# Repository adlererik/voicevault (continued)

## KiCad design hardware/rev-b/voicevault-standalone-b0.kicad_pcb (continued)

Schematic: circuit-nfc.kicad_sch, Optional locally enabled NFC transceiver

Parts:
C1001, C1003, C1007, C1009, C1016: 2.2u 10V; C_0603_1608Metric
C1002: 100n 10V; C_0402_1005Metric
C1004, C1006, C1008, C1010, C1013: 10n 10V; C_0402_1005Metric
C1005: 4.7u 10V; C_0603_1608Metric
C1011: 22n 10V; C_0402_1005Metric
C1012: 1u 10V; C_0603_1608Metric
C1014, C1015: 10p C0G; C_0402_1005Metric
R1001: 100k; R_0402_1005Metric
R1002: 47k; R_0402_1005Metric
U7: ST25R3916B-BWLT; ST25R3916B_WLCSP36_REVIEW
U1001: TLV75533PDRVR; TI_DRV0006A_WSON6_2x2_EP1x1p6
X1001: 830108212709 / 27.12MHz CL8pF; Crystal_SMD_2016-4Pin_2.0x1.6mm

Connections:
GND: C1001.2, C1002.2, C1003.2, C1004.2, C1005.2, C1006.2, C1007.2, C1008.2, C1009.2, C1010.2, C1011.2, C1012.2, C1013.2, C1014.2, C1015.2, C1016.2, R1001.2, U7.A3 (GND_A), U7.B3 (GND_A), U7.B4 (GND_A), U7.C1 (VSS), U7.C2 (VSS), U7.C3 (VSS), U7.D2 (I2C_EN), U7.D5 (GND_D), U7.F1 (GND_DR2), U7.F4 (GND_DR1), U1001.3 (GND), U1001.7 (EP_GND), X1001.2 (CASE), X1001.4 (CASE); also elsewhere on the board
NFC_3V3: C1001.1, C1002.1, C1003.1, C1004.1, R1002.2, U7.A6 (VDD_IO), U7.E5 (VDD_TX), U7.E6 (VDD), U1001.1 (OUT); also elsewhere on the board
NFC_AGDC: C1012.1, C1013.1, U7.A2 (AGDC)
NFC_CS_N: R1002.1, U7.A5 (BSS); also elsewhere on the board
NFC_IRQ: U7.A4 (IRQ); also elsewhere on the board
NFC_MISO: U7.B5 (MISO); also elsewhere on the board
NFC_MOSI: U7.D4 (MOSI); also elsewhere on the board
NFC_POWER_EN: R1001.1, U1001.4 (EN); also elsewhere on the board
NFC_RFI1: U7.B1 (RFI1); also elsewhere on the board
NFC_RFI2: U7.B2 (RFI2); also elsewhere on the board
NFC_RFO1: U7.F3 (RFO1); also elsewhere on the board
NFC_RFO2: U7.F2 (RFO2); also elsewhere on the board
NFC_RF_DR: C1005.1, C1006.1, U7.E3 (VDD_DR), U7.F6 (VDD_RF)
NFC_SCK: U7.D3 (SCLK); also elsewhere on the board
NFC_VDD_A: C1009.1, C1010.1, U7.E4 (VDD_A)
NFC_VDD_AM: C1011.1, U7.F5 (VDD_AM)
NFC_VDD_D: C1007.1, C1008.1, U7.C5 (VDD_D)
NFC_XTI: C1014.1, U7.D6 (XTI), X1001.1 (XI)
NFC_XTO: C1015.1, U7.C6 (XTO), X1001.3 (XO)
VSYS: C1016.1, U1001.6 (IN); also elsewhere on the board

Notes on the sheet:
ST25R3916B-BWLT retains Safe7 core part. Supplies/decoupling and crystal follow pinned TS7 sheet10 and ST DS13541.
Dedicated VSYS LDO avoids overloading the MCU 200mA buck. Default power off and signal bridge disabled.
No NFC use during calls or charging tests until RF/thermal/current limits and trusted local pairing are defined.
IRQ is active HIGH. TAD/clock/automatic-tuning outputs unused. Fixed matching network is on the following sheet.
NFC transport alone does not authenticate a contact; device signatures/pinned contacts and local confirmation remain mandatory.

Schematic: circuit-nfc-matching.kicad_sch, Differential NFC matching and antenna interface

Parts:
C1017, C1018: 680p C0G 50V; C_0402_1005Metric
C1019, C1020: 150p C0G 50V; C_0402_1005Metric
C1021, C1022: 68p C0G 50V; C_0402_1005Metric
C1023, C1024: 10p C0G 50V; C_0402_1005Metric
C1025, C1026: 180p C0G 50V; C_0402_1005Metric
J1001: BM02B-SRSS-TB(LF)(SN); NFC ANTENNA; JST_SH_BM02B-SRSS-TB_1x02-1MP_P1.00mm_Vertical
L1001, L1002: 270nH RF; L_0603_1608Metric
R1003, R1004: 2R 1%; R_0402_1005Metric

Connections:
GND: C1017.2, C1018.2, C1021.2, C1022.2, C1025.2, C1026.2; also elsewhere on the board
NFC_ANT1: J1001.1 (ANT_1), R1003.2
NFC_ANT2: J1001.2 (ANT_2), R1004.2
NFC_EMC1: C1017.1, C1019.1, L1001.2
NFC_EMC2: C1018.1, C1020.1, L1002.2
NFC_MATCH1: C1019.2, C1021.1, C1023.1, R1003.1
NFC_MATCH2: C1020.2, C1022.1, C1024.1, R1004.1
NFC_RFI1: C1023.2, C1025.1; also elsewhere on the board
NFC_RFI2: C1024.2, C1026.1; also elsewhere on the board
NFC_RFO1: L1001.1; also elsewhere on the board
NFC_RFO2: L1002.1; also elsewhere on the board

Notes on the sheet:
Matching topology/starting values from Safe7 TS7 revD sheet10. They are NOT validated for a replacement antenna.
Pulse W7001 is a catalogue antenna candidate; confirm supply, dimensions, inductance/Q and cable before release.
Require VNA matching, field strength, coexistence, ferrite/metal-stack and temperature tests on the actual assembly.
Keep NFC disabled until antenna/current/thermal and pairing-protocol qualification passes.

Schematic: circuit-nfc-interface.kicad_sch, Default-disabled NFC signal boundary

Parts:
C1027, C1028, C1029, C1030: 100n 10V; C_0402_1005Metric
R1005, R1006: 100k; R_0402_1005Metric
U1002, U1003: SN74AXC4T774PWR; TSSOP-16_4.4x5mm_P0.65mm

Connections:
GND: C1027.2, C1028.2, C1029.2, C1030.2, R1006.2, U1002.7 (DIR3), U1002.10 (GND), U1003.1 (DIR1), U1003.4 (A2), U1003.5 (A3), U1003.6 (A4), U1003.10 (GND); also elsewhere on the board
NFC_3V3: C1028.1, C1030.1, U1002.15 (VCCB), U1003.15 (VCCB); also elsewhere on the board
NFC_CS_N: U1002.11 (B4); also elsewhere on the board
NFC_HOST_CS_N: U1002.6 (A4); also elsewhere on the board
NFC_HOST_IRQ: R1006.1, U1003.3 (A1); also elsewhere on the board
NFC_HOST_MISO: U1002.5 (A3); also elsewhere on the board
NFC_HOST_MOSI: U1002.4 (A2); also elsewhere on the board
NFC_HOST_SCK: U1002.3 (A1); also elsewhere on the board
NFC_IO_DISABLE: R1005.1, U1002.9 (OE_N), U1003.9 (OE_N); also elsewhere on the board
NFC_IRQ: U1003.14 (B1); also elsewhere on the board
NFC_MISO: U1002.12 (B3); also elsewhere on the board
NFC_MOSI: U1002.13 (B2); also elsewhere on the board
NFC_SCK: U1002.14 (B1); also elsewhere on the board
VDD_3V3: C1027.1, C1029.1, R1005.2, U1002.1 (DIR1), U1002.2 (DIR2), U1002.8 (DIR4), U1002.16 (VCCA), U1003.2 (DIR2), U1003.7 (DIR3), U1003.8 (DIR4), U1003.16 (VCCA); also elsewhere on the board

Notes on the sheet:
SPI1 PA5/PA6/PA7, GPIO PA4 CS, PG9 active-high IRQ; no shared radio, secure-element or PMIC bus.
Strapped directions and default-high OE keep NFC signals disconnected through reset and power changes.
Check VCC isolation, power-off leakage and interrupt-flood bounds on the assembled prototype.

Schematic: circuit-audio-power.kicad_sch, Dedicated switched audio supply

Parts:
C614, C615: 2.2u 10V; C_0603_1608Metric
R608: 100k; R_0402_1005Metric
R609: 0R - removable audio-current link; R_0603_1608Metric
U602: TLV75533PDRVR; TI_DRV0006A_WSON6_2x2_EP1x1p6

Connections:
AUD_3V3_REG: C615.1, R609.1, U602.1 (OUT)
AUD_LDOIN_3V3: R609.2; also elsewhere on the board
AUD_POWER_EN: R608.1, U602.4 (EN); also elsewhere on the board
GND: C614.2, C615.2, R608.2, U602.3 (GND), U602.7 (EP_GND); also elsewhere on the board
VSYS: C614.1, U602.6 (IN); also elsewhere on the board

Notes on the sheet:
Do not place the codec analog/headphone supply on the 200mA MCU buck: TI calls for 150mA analog capability plus digital demand.
PB10 enable has a 100k pulldown. IOVDD must be valid before LDOIN; hold audio RESET and clocks low during startup.
After MCU rail/configuration readback, enable LDOIN; verify rail and internal DLDO, then release RESET and wait >=1ms before writes.
R609 is a removable current-measurement link. VSYS dropout and output discharge/restart require bench tests.
DRV WSON thermal pad must connect to ground/copper heat spreading; 500mA rating is not a continuous thermal allocation.
The TLV755 input/output capacitors must retain >0.47uF effective capacitance after DC bias, tolerance and temperature.

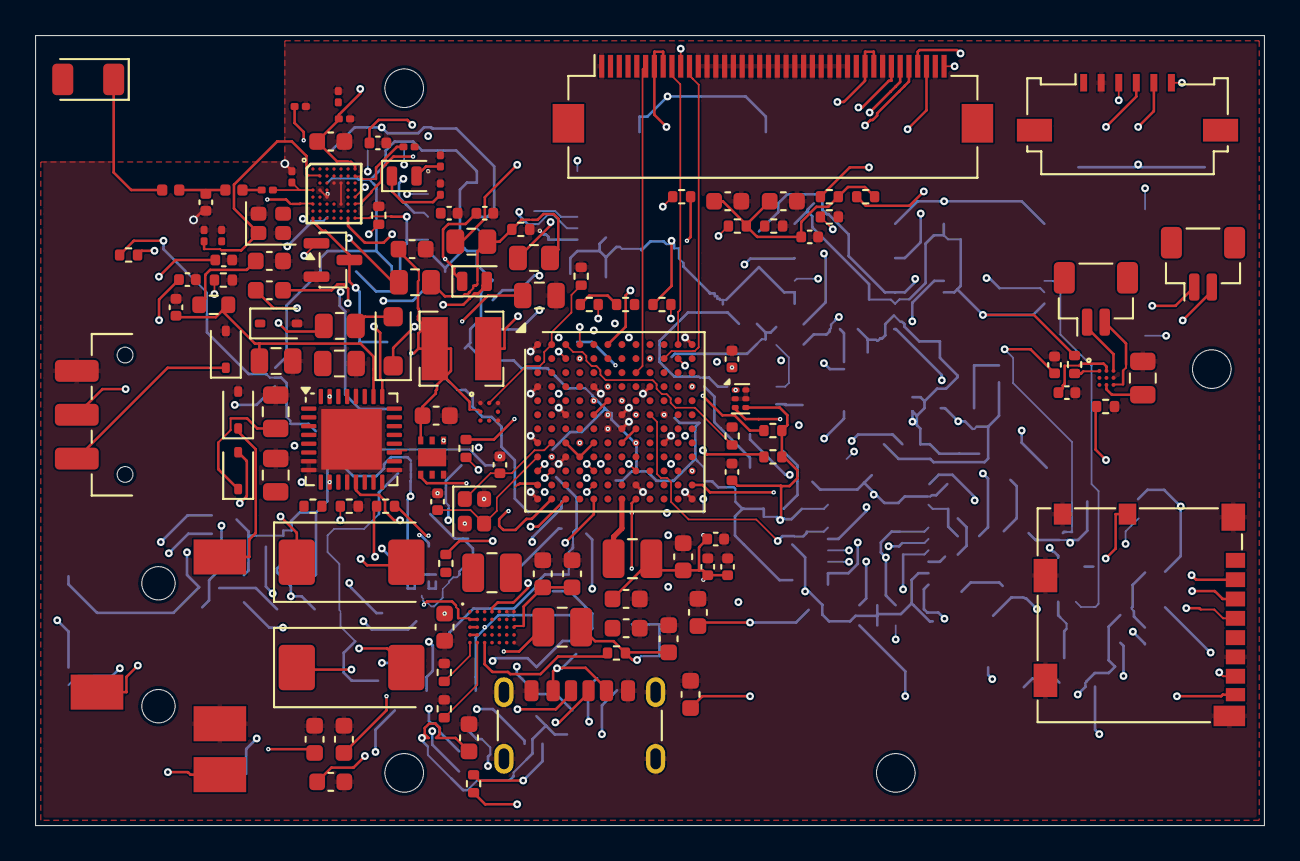
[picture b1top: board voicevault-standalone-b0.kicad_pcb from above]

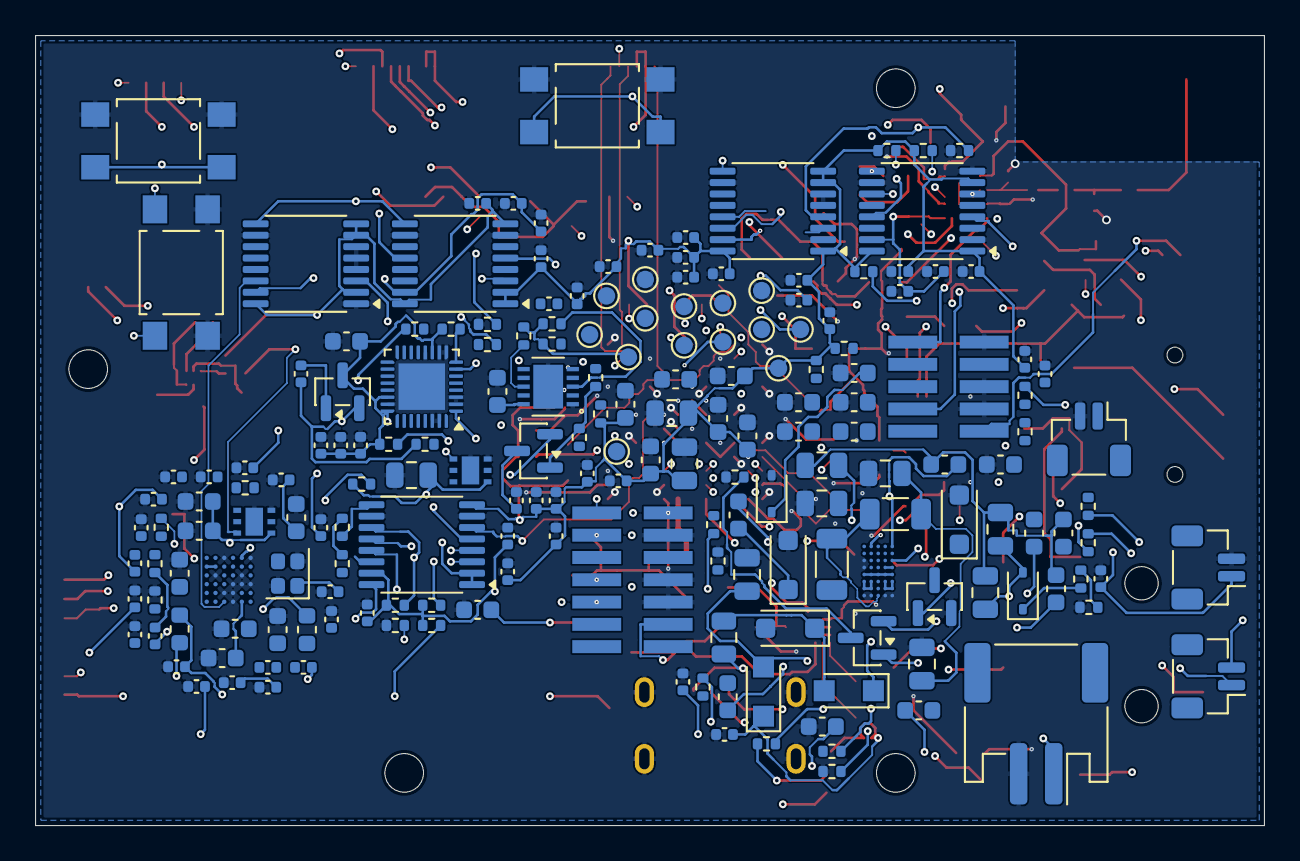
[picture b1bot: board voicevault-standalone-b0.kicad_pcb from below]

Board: 6 copper layers, 70.0 x 45.0 mm, 314 parts (189 on the bottom side), 199 nets.

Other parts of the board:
H1, H2, H3, H4: M2 mounting hole / not an assembled component; MountingHole_2.2mm_M2
TP1: PROBE VSYS; TestPoint_Pad_D1.0mm
TP2, TP14: PROBE GND; TestPoint_Pad_D1.0mm
TP3: PROBE VDD_3V3; TestPoint_Pad_D1.0mm
TP4: PROBE AUX_3V3; TestPoint_Pad_D1.0mm
TP5: PROBE MCU_VDD11; TestPoint_Pad_D1.0mm
TP6: PROBE RADIO_3V3; TestPoint_Pad_D1.0mm
TP7: PROBE TR_3V3; TestPoint_Pad_D1.0mm
TP8: PROBE OP_3V3; TestPoint_Pad_D1.0mm
TP9: PROBE SD_3V3; TestPoint_Pad_D1.0mm
TP10: PROBE NFC_3V3; TestPoint_Pad_D1.0mm
TP11: PROBE AUD_LDOIN_3V3; TestPoint_Pad_D1.0mm
TP12: PROBE QI_5V; TestPoint_Pad_D1.0mm
TP13: PROBE BAT_PACK; TestPoint_Pad_D1.0mm

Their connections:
AUD_LDOIN_3V3: TP11.1; also elsewhere on the board
AUX_3V3: TP4.1; also elsewhere on the board
BAT_PACK: TP13.1; also elsewhere on the board
GND: TP2.1, TP14.1; also elsewhere on the board
MCU_VDD11: TP5.1; also elsewhere on the board
NFC_3V3: TP10.1; also elsewhere on the board
OP_3V3: TP8.1; also elsewhere on the board
QI_5V: TP12.1; also elsewhere on the board
RADIO_3V3: TP6.1; also elsewhere on the board
SD_3V3: TP9.1; also elsewhere on the board
TR_3V3: TP7.1; also elsewhere on the board
VDD_3V3: TP3.1; also elsewhere on the board
VSYS: TP1.1; also elsewhere on the board

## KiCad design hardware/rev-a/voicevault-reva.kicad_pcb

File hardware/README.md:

# VoiceVault hardware laboratory

The active design is the **[standalone Rev B prototype](rev-b/README.md)**: a rectangular 70 × 45 mm SMD board using Safe 7 core ICs, with audio, microSD, independent debug interfaces and sourceable display/battery candidates. It contains **296 electrical components, 14 probe pads and four mounting holes**. The complete-board FreeRouting result has been imported through kipy and its copper zones refilled. Native KiCad reports **280 open connections, 33 layout errors and 100 warnings**. [Actual run and final DRC](evidence/2026-11-12/autoroute/README.md). **Manufacturing remains blocked.** [Status](rev-b/STATUS.json) · [Actual B0 images and results](evidence/2026-11-12/README.md)

## Open the active PCB

Run `./hardware/open` from the repository. It opens only the PCB editor required for MCP and reuses an existing copy. This computer previously ran out of memory when several CAD/emulator windows were opened together. Keep the schematic/3D/emulators closed during heavier jobs. The older `--all` launcher targets the historical Rev A demonstration and is not the active B0 workflow.

Installed tools: **KiCad 10.0.8, ngspice 47, Renode 1.17.0, QEMU 9.2.4**, **Freerouting 2.5.0** and **kicad-tools 0.29.0** for bounded routing studies. [Exact tool records](reference/tools.json)

KiCad editor interaction uses MCP through official IPC. Native KiCad generation/exports/ERC/DRC and ngspice runs use direct command-line tools. This keeps inputs, outputs and failures reproducible and inspectable without requiring a separate MCP server for every executable. Renode currently lacks the required STM32U5G peripherals; QEMU runs CPU-only diagnostics. Neither is a qualified full-device emulator.

## Local KiCad MCP

The enabled stdio server `voicevault-kicad`, launched by `hardware/mcp`, uses the official MCP SDK and KiCad Python IPC bindings. It checks the exact active B0 board path and exposes status, footprint positions, named nets, an undoable footprint move and save. It does not expose a schematic-editing API or program a physical MCU.

The environment uses **managed CPython 3.12.14**, independent of system Python updates. Recreate it with:

```sh
python3 hardware/tools/setup_design_env.py
python3 hardware/tools/setup_kicad.py --enable-api
```

This requires `uv` and KiCad with its symbol/footprint/3D library extensions. Register the absolute `hardware/mcp` launcher with `codex mcp add voicevault-kicad -- /absolute/path/to/hardware/mcp`, then run `./hardware/open`. An existing Codex session may need reopening to discover newly registered tools; the MCP stdio connection can also be verified directly. The local IPC socket is under the KiCad Flatpak cache at `vv-pcb/kicad/api.sock`. No network listener is used by MCP.

The latest live check read **314 footprints and 199 named nets** from the open B0 editor. Evidence is stored with the dated B0 results. The earlier 30-footprint Rev A MCP result is historical.

Current 2D rendering uses **software/Cairo** to avoid the recurring OpenGL loader error. GPU/OpenGL startup is not claimed fixed. The setup helper saves library tables and first-run choices. The native generator now attaches rear-side footprints to the board before flipping them; doing that in the opposite order triggered KiCad's bundled Python 3.14 crash. This is separate from the pinned MCP Python environment.

## Available checks

```sh
./hardware/check --design-only --spice
```

Results and raw logs go to `.lab-runs/hardware/standalone-b0/`. The checks compare the actual native schematic and copper-pad net assignments, verify independent ST ball/function data, run ERC/DRC, test the antenna keepout with deliberately forbidden copper on a copy, exercise the copper-import guard on deliberately valid/invalid proposals, execute **799 ngspice passive/static cases** when `--spice` is selected, and compute a clearly labeled power-allocation study.

`--design-only` exits 0 when those available checks pass, **while keeping the manufacturing verdict blocked**. Without it, exit 2 means manufacturing is blocked. Exit 1 means an available check failed. DRC's list is capped, so remaining routing work is counted from KiCad's full ratsnest rather than the first 499 listed items.

Install ngspice 47 on another host, or point `VOICEVAULT_NGSPICE` to its executable. The scripts prefer this computer's verified cached installation when present. [SPICE models and limits](rev-b/SPICE_RESULTS.md) · [Power/circuit review](rev-b/CIRCUIT_REVIEW.md)

The latest whole-board run used the official, unmodified **FreeRouting 2.5.0 JAR on OpenJDK 25.0.4.1**, with bounded memory/CPU use and a 30-minute application deadline. It saved an SES at the deadline. KiCad’s native SES reader decoded it on a copy; a copper-only kipy transaction applied the complete result to the live board. The earlier timed-out studies were not applied. The current global result fails native DRC and is an unfinished checkpoint. Autorouting does not qualify BGA escape geometry, RF matching, return planes, power loops or a manufacturing stackup.

## Target and qualification

[Active B0 target](rev-b/target.json) is **STM32U5G9ZJJ6Q UFBGA144**. [Earlier bench reference](reference/target.json) is the DK2's **STM32U5G9ZJT6Q LQFP144**. Keep those identities distinct. The B0 revision, option bytes, entropy, audio/DMA interrupts, forbidden-access denial, clocks, supply behavior, radio isolation, acoustics, RF, charging and thermals remain unmeasured.

The software's hardware-evidence contract rejects absent models, warning-producing register accesses, missing samples/interrupts/denials and timeouts. A synthetic trace is a test of the checker, not evidence about physical silicon. CPU-only crypto/Opus memory results remain scoped to their recorded configurations.

## Historical Rev A carrier

`hardware/rev-a/` preserves the earlier 150 × 120 mm cabled DK2 carrier, module BOM and wiring plan. It is not the custom B0 device and is also unrouted. Run `./hardware/check --rev-a --design-only` for its 22 older circuit cases and actual Renode missing-peripheral negative control. [2026-11-11 evidence](evidence/2026-11-11/README.md) preserves those results. The [NUCLEO-U5A5 assessment](reference/NUCLEO_U5A5_ASSESSMENT.md) remains a reference comparison, not the active compute module.

## Assembly

[Manufacturing cost research](rev-b/MANUFACTURING_COST.md) compares public capabilities/fees for four assemblies delivered to Sweden. A cheapest delivered supplier is not established. Routing proceeds against provisional published constraints while quotations are deferred.

The [B0 circuit inventory](rev-b/circuit-inventory.csv) is not an approved assembly BOM. Exact part/variant acceptance, HDI stackup, land patterns, routing, power/thermal review, DFM/CPL, fixtures and physical qualification remain open. Batteries and other external assemblies need explicitly agreed handling; a populated PCB is not automatically a complete enclosed device. Nothing has been ordered or submitted for manufacture.

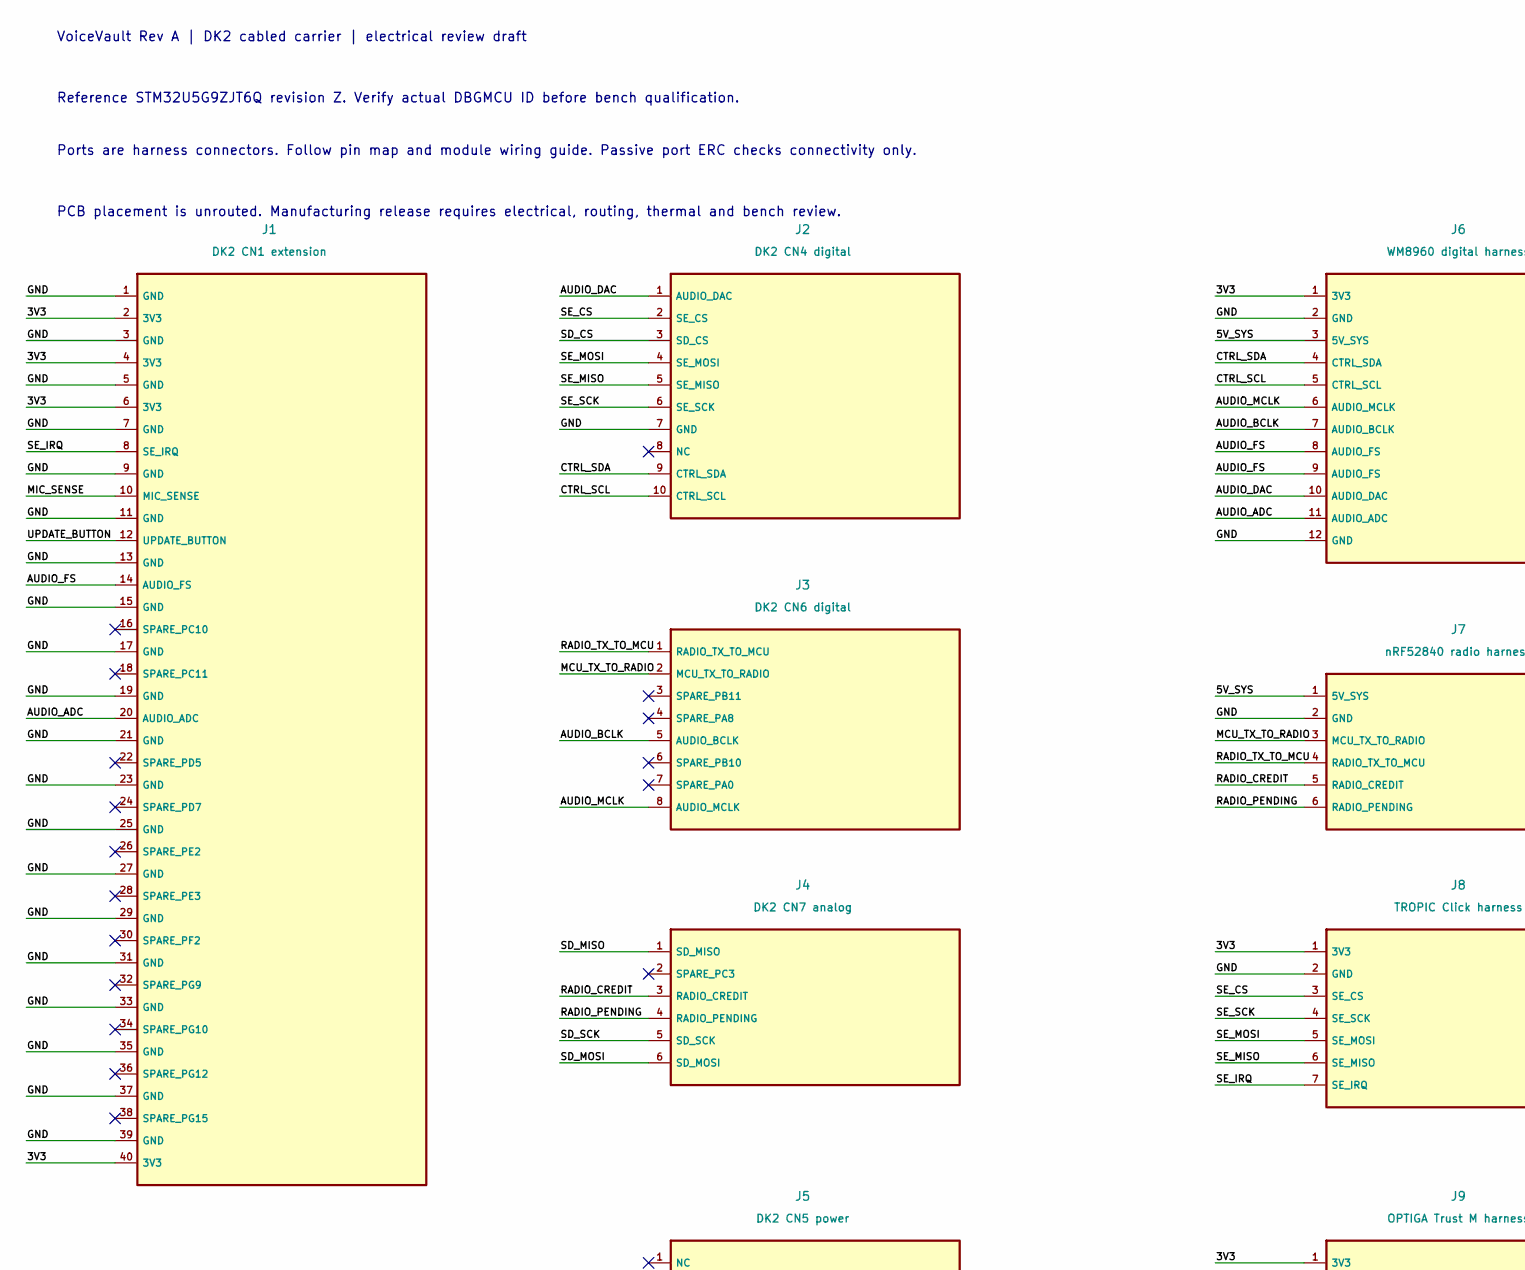
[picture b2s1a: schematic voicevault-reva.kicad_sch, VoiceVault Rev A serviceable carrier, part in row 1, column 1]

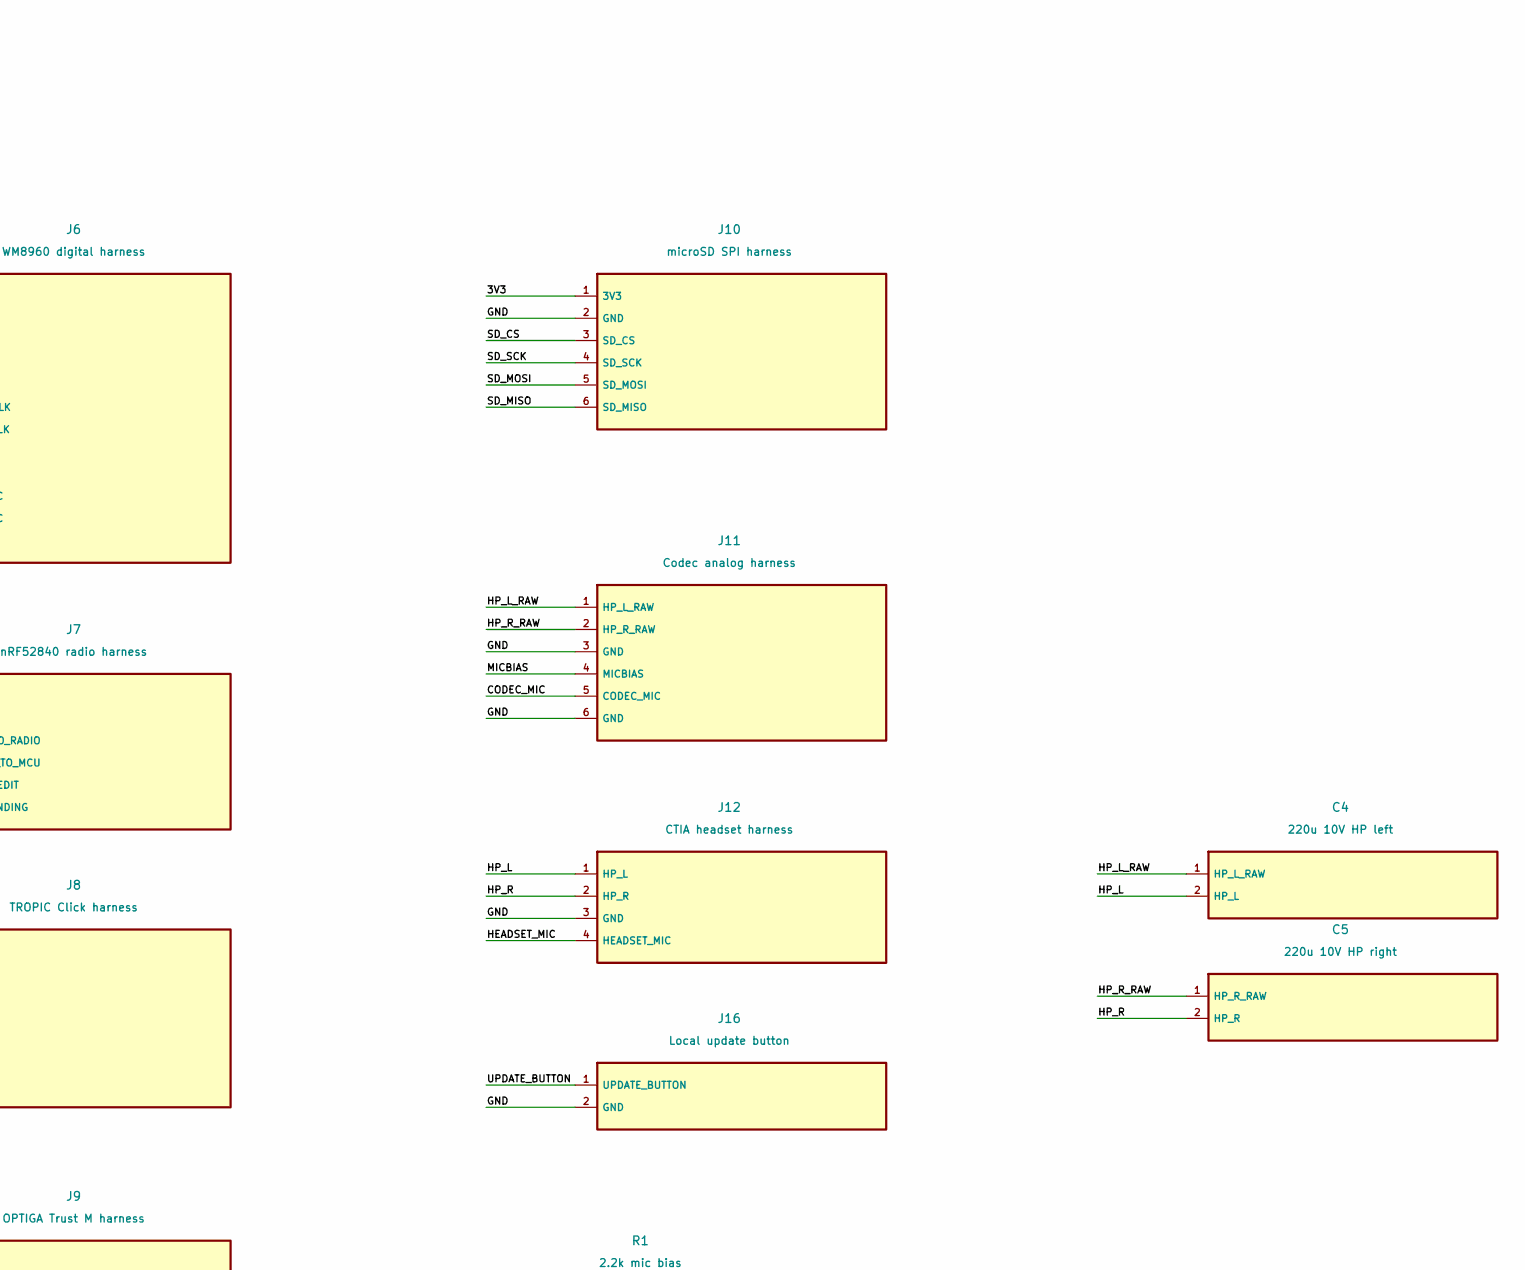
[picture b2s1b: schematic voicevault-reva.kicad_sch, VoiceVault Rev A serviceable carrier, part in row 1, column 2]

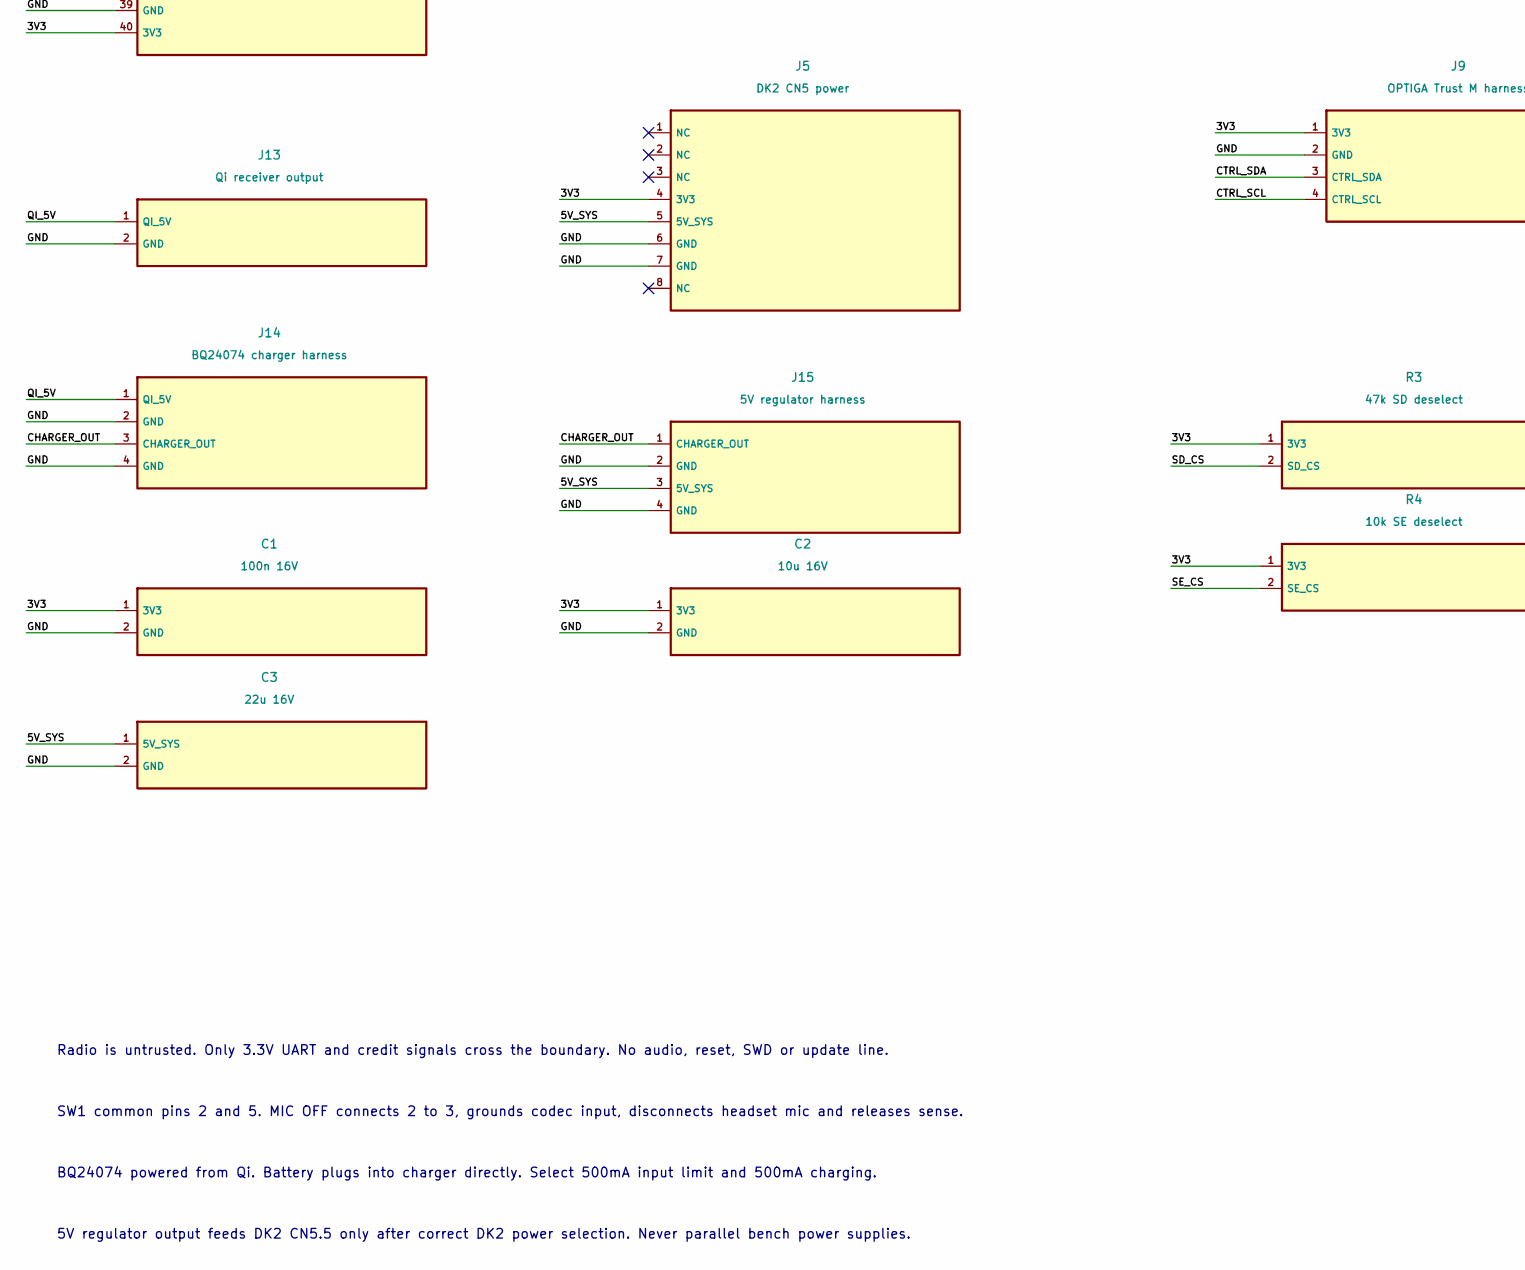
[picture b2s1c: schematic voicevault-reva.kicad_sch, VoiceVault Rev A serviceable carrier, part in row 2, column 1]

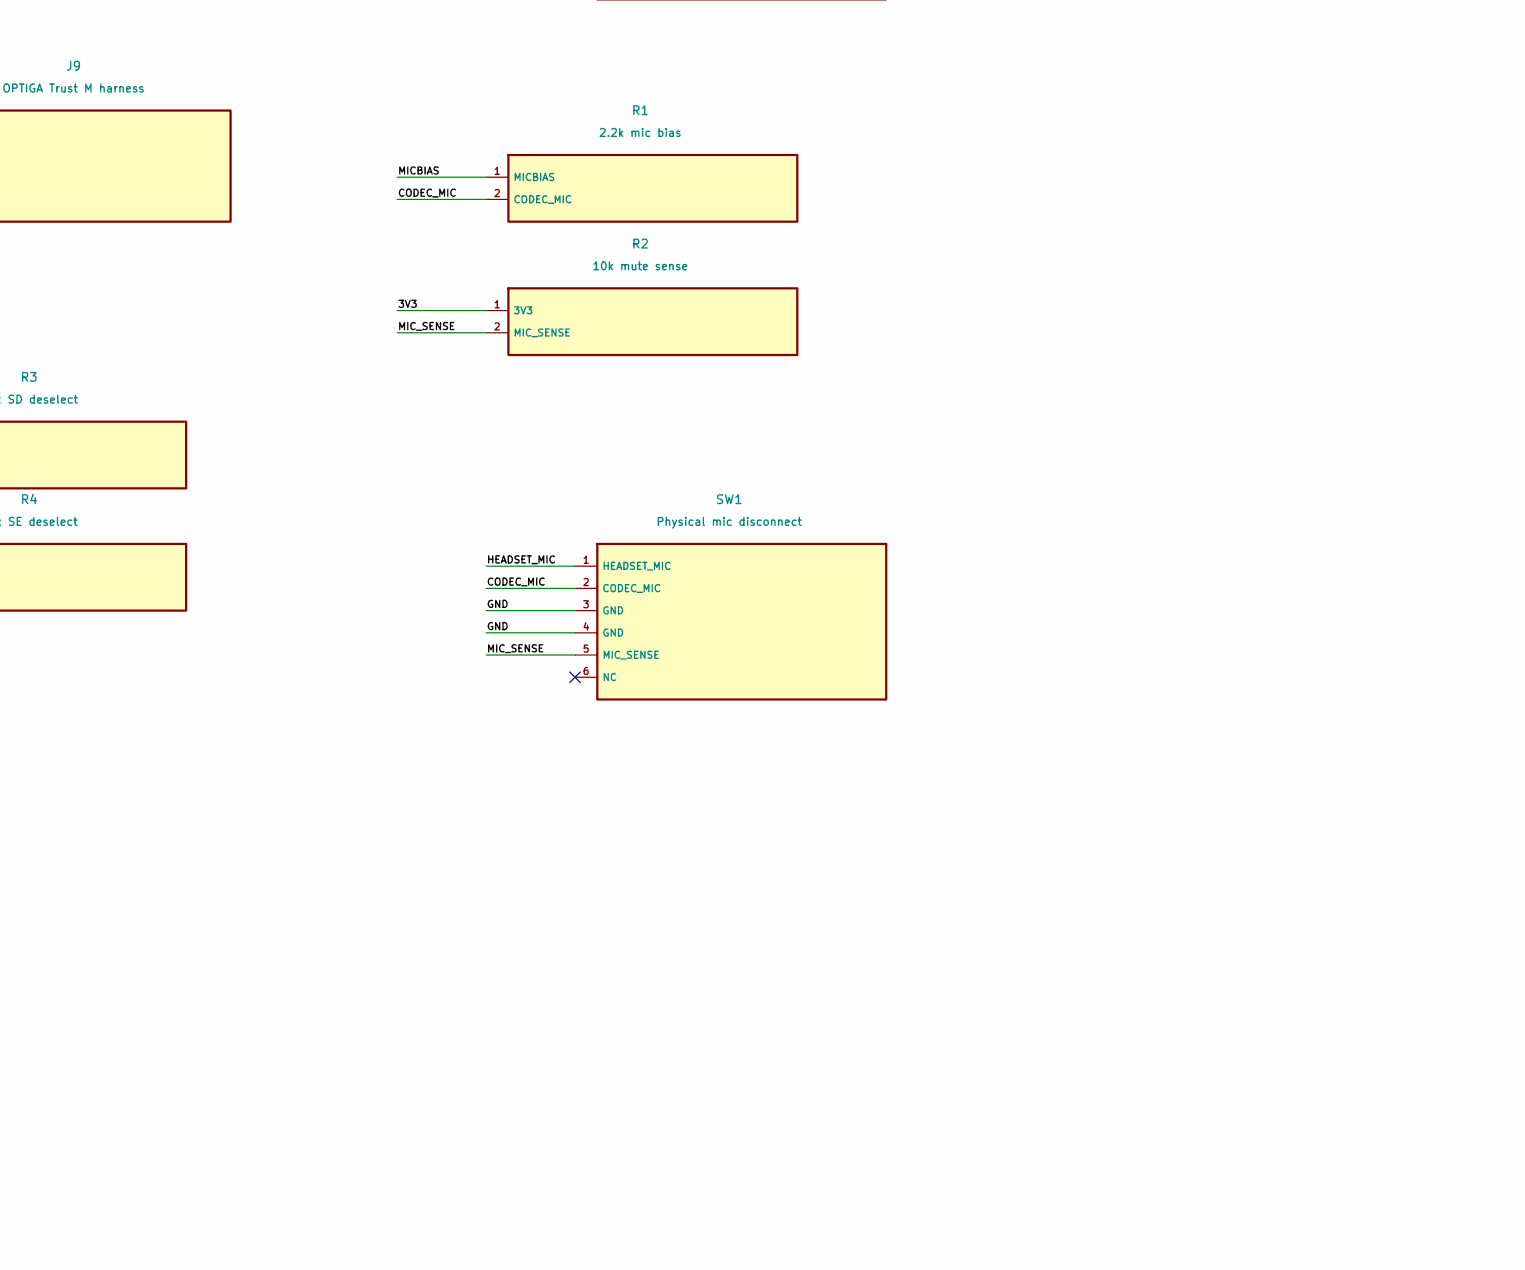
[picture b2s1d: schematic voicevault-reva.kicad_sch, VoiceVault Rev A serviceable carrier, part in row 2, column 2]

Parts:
C1: 100n 16V; C_0603_1608Metric
C2: 10u 16V; C_0805_2012Metric
C3: 22u 16V; C_1210_3225Metric
C4: 220u 10V HP left; CP_Radial_D6.3mm_P2.50mm
C5: 220u 10V HP right; CP_Radial_D6.3mm_P2.50mm
J1: DK2 CN1 extension; PinHeader_2x20_P2.54mm_Vertical
J2: DK2 CN4 digital; PinHeader_1x10_P2.54mm_Vertical
J3: DK2 CN6 digital; PinHeader_1x08_P2.54mm_Vertical
J4: DK2 CN7 analog; PinHeader_1x06_P2.54mm_Vertical
J5: DK2 CN5 power; PinHeader_1x08_P2.54mm_Vertical
J6: WM8960 digital harness; PinHeader_1x12_P2.54mm_Vertical
J7: nRF52840 radio harness; PinHeader_1x06_P2.54mm_Vertical
J8: TROPIC Click harness; PinHeader_1x07_P2.54mm_Vertical
J9: OPTIGA Trust M harness; PinHeader_1x04_P2.54mm_Vertical
J10: microSD SPI harness; PinHeader_1x06_P2.54mm_Vertical
J11: Codec analog harness; PinHeader_1x06_P2.54mm_Vertical
J12: CTIA headset harness; PinHeader_1x04_P2.54mm_Vertical
J13: Qi receiver output; PinHeader_1x02_P2.54mm_Vertical
J14: BQ24074 charger harness; PinHeader_1x04_P2.54mm_Vertical
J15: 5V regulator harness; PinHeader_1x04_P2.54mm_Vertical
J16: Local update button; PinHeader_1x02_P2.54mm_Vertical
R1: 2.2k mic bias; R_0603_1608Metric
R2: 10k mute sense; R_0603_1608Metric
R3: 47k SD deselect; R_0603_1608Metric
R4: 10k SE deselect; R_0603_1608Metric
SW1: Physical mic disconnect; SW_CK_JS202011CQN_DPDT_Straight

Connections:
3V3: C1.1 (3V3), C2.1 (3V3), J1.2 (3V3), J1.4 (3V3), J1.6 (3V3), J1.40 (3V3), J5.4 (3V3), J6.1 (3V3), J8.1 (3V3), J9.1 (3V3), J10.1 (3V3), R2.1 (3V3), R3.1 (3V3), R4.1 (3V3)
5V_SYS: C3.1 (5V_SYS), J5.5 (5V_SYS), J6.3 (5V_SYS), J7.1 (5V_SYS), J15.3 (5V_SYS)
AUDIO_ADC: J1.20 (AUDIO_ADC), J6.11 (AUDIO_ADC)
AUDIO_BCLK: J3.5 (AUDIO_BCLK), J6.7 (AUDIO_BCLK)
AUDIO_DAC: J2.1 (AUDIO_DAC), J6.10 (AUDIO_DAC)
AUDIO_FS: J1.14 (AUDIO_FS), J6.8 (AUDIO_FS), J6.9 (AUDIO_FS)
AUDIO_MCLK: J3.8 (AUDIO_MCLK), J6.6 (AUDIO_MCLK)
CHARGER_OUT: J14.3 (CHARGER_OUT), J15.1 (CHARGER_OUT)
CODEC_MIC: J11.5 (CODEC_MIC), R1.2 (CODEC_MIC), SW1.2 (CODEC_MIC)
CTRL_SCL: J2.10 (CTRL_SCL), J6.5 (CTRL_SCL), J9.4 (CTRL_SCL)
CTRL_SDA: J2.9 (CTRL_SDA), J6.4 (CTRL_SDA), J9.3 (CTRL_SDA)
GND: C1.2 (GND), C2.2 (GND), C3.2 (GND), J1.1 (GND), J1.3 (GND), J1.5 (GND), J1.7 (GND), J1.9 (GND), J1.11 (GND), J1.13 (GND), J1.15 (GND), J1.17 (GND), J1.19 (GND), J1.21 (GND), J1.23 (GND), J1.25 (GND), J1.27 (GND), J1.29 (GND), J1.31 (GND), J1.33 (GND), J1.35 (GND), J1.37 (GND), J1.39 (GND), J2.7 (GND), J5.6 (GND), J5.7 (GND), J6.2 (GND), J6.12 (GND), J7.2 (GND), J8.2 (GND), J9.2 (GND), J10.2 (GND), J11.3 (GND), J11.6 (GND), J12.3 (GND), J13.2 (GND), J14.2 (GND), J14.4 (GND), J15.2 (GND), J15.4 (GND), J16.2 (GND), SW1.3 (GND), SW1.4 (GND)
HEADSET_MIC: J12.4 (HEADSET_MIC), SW1.1 (HEADSET_MIC)
HP_L: C4.2 (HP_L), J12.1 (HP_L)
HP_L_RAW: C4.1 (HP_L_RAW), J11.1 (HP_L_RAW)
HP_R: C5.2 (HP_R), J12.2 (HP_R)
HP_R_RAW: C5.1 (HP_R_RAW), J11.2 (HP_R_RAW)
MCU_TX_TO_RADIO: J3.2 (MCU_TX_TO_RADIO), J7.3 (MCU_TX_TO_RADIO)
MICBIAS: J11.4 (MICBIAS), R1.1 (MICBIAS)
MIC_SENSE: J1.10 (MIC_SENSE), R2.2 (MIC_SENSE), SW1.5 (MIC_SENSE)
QI_5V: J13.1 (QI_5V), J14.1 (QI_5V)
RADIO_CREDIT: J4.3 (RADIO_CREDIT), J7.5 (RADIO_CREDIT)
RADIO_PENDING: J4.4 (RADIO_PENDING), J7.6 (RADIO_PENDING)
RADIO_TX_TO_MCU: J3.1 (RADIO_TX_TO_MCU), J7.4 (RADIO_TX_TO_MCU)
SD_CS: J2.3 (SD_CS), J10.3 (SD_CS), R3.2 (SD_CS)
SD_MISO: J4.1 (SD_MISO), J10.6 (SD_MISO)
SD_MOSI: J4.6 (SD_MOSI), J10.5 (SD_MOSI)
SD_SCK: J4.5 (SD_SCK), J10.4 (SD_SCK)
SE_CS: J2.2 (SE_CS), J8.3 (SE_CS), R4.2 (SE_CS)
SE_IRQ: J1.8 (SE_IRQ), J8.7 (SE_IRQ)
SE_MISO: J2.5 (SE_MISO), J8.6 (SE_MISO)
SE_MOSI: J2.4 (SE_MOSI), J8.5 (SE_MOSI)
SE_SCK: J2.6 (SE_SCK), J8.4 (SE_SCK)
UPDATE_BUTTON: J1.12 (UPDATE_BUTTON), J16.1 (UPDATE_BUTTON)

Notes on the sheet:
VoiceVault Rev A | DK2 cabled carrier | electrical review draft
Reference STM32U5G9ZJT6Q revision Z. Verify actual DBGMCU ID before bench qualification.
Ports are harness connectors. Follow pin map and module wiring guide. Passive port ERC checks connectivity only.
PCB placement is unrouted. Manufacturing release requires electrical, routing, thermal and bench review.
Radio is untrusted. Only 3.3V UART and credit signals cross the boundary. No audio, reset, SWD or update line.
SW1 common pins 2 and 5. MIC OFF connects 2 to 3, grounds codec input, disconnects headset mic and releases sense.
BQ24074 powered from Qi. Battery plugs into charger directly. Select 500mA input limit and 500mA charging.
5V regulator output feeds DK2 CN5.5 only after correct DK2 power selection. Never parallel bench power supplies.

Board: 2 copper layers, 30 parts (0 on the bottom side), 34 nets, no tracks yet.

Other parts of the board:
H1, H2, H3, H4: MountingHole_3.2mm_M3

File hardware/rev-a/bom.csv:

Reference,Quantity,Manufacturer,Candidate part number,Purpose,Manufacturer source,Review status
MOD1,1,STMicroelectronics,STM32U5G9J-DK2,MCU and trusted LCD reference assembly,https://www.st.com/en/evaluation-tools/stm32u5g9j-dk2.html,Reference Z silicon requires actual ID check
MOD2,1,SparkFun,BOB-21772,WM8960 codec breakout with headers,https://github.com/sparkfun/SparkFun_Audio_Codec_Breakout_WM8960,Bench module only; codec discontinued; active TI TLV320AIC3204 candidate for later design
MOD3,1,Adafruit,4062,nRF52840 Feather untrusted radio module,https://www.adafruit.com/product/4062,Custom bounded ciphertext-only UART firmware pending
MOD4,1,MikroElektronika,MIKROE-6559,Secure Tropic Click,https://www.mikroe.com/secure-tropic-click,Confirm exact TROPIC01 silicon and driver operations
MOD5,1,Infineon,S2GO-SECURITY-OPTIGA-M,OPTIGA Trust M evaluation board,https://www.infineon.com/evaluation-board/S2GO-SECURITY-OPTIGA-M,I2C harness; hardware key mapping pending
MOD6,1,Adafruit,4682,3V microSD breakout,https://www.adafruit.com/product/4682,Dedicated software SPI update interface
MOD7,1,Adafruit,1901,5V 500mA Qi receiver,https://www.adafruit.com/product/1901,Vendor has changed chip revisions; verify received module
MOD8,1,Adafruit,4755,BQ24074 charger and load sharing,https://www.adafruit.com/product/4755,Configure input and charging limits to 500mA and fit NTC
MOD9,1,Pololu,4082 / S13V30F5,5V buck-boost regulator module,https://www.pololu.com/product/4082,Review efficiency and standby current for final device
BAT1,1,Adafruit,353,Protected 3.7V 6600mAh battery pack,https://www.adafruit.com/product/353,Bench pack; under 1.3A sustained vendor recommendation
NTC1,1,Semitec,103AT-2,10k NTC battery temperature sensor,https://www.semitec-global.com/product/at-thermistor/,Check charger temperature thresholds; attach to pack
JACK1,1,Adafruit,2915,TRRS jack terminal adapter,https://www.adafruit.com/product/2915,Use CTIA wiring by contact continuity
SW1,1,C&K,JS202011CQN,Mechanical DPDT microphone disconnect,https://www.ckswitches.com/products/switches/product-details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,Verify pin and throw numbering against received part
SW2,1,E-Switch,TL1105AF160Q,Offboard local update pushbutton,https://www.e-switch.com/product-catalog/tl1105-series-tact-switch/,Connect J16 to ground when pressed
R1,1,Yageo,RC0603FR-072K2L,2.2k 1% 0603 mic bias,https://www.yageo.com/en/Product/Index/rchip,Candidate procurement MPN requires datasheet review
R2 R4,2,Yageo,RC0603FR-0710KL,10k 1% 0603 sense and CS pullup,https://www.yageo.com/en/Product/Index/rchip,Candidate procurement MPN requires datasheet review
R3,1,Yageo,RC0603FR-0747KL,47k 1% 0603 SD CS pullup,https://www.yageo.com/en/Product/Index/rchip,Candidate procurement MPN requires datasheet review
C1,1,Murata,GRM188R71C104KA01D,100n 16V X7R 0603,https://www.murata.com/en-global/products/capacitor/ceramicc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,Verify exact dimensions and bias derating
C2,1,Murata,GRM21BR61C106KE15L,10u 16V X5R 0805,https://www.murata.com/en-global/products/capacitor/ceramicc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,Verify effective capacitance at operating bias
C3,1,KEMET,C1210C226K4PACTU,22u 16V 1210 bulk capacitor,https://www.kemet.com/en/us/capacitors/ceramic.html,Candidate MPN; confirm voltage package and effective capacitance
C4 C5,2,Nichicon,UKL1A221KDD,220u 10V low leakage polarized headphone coupling,https://www.nichicon.co.jp/english/products/aluminum/,Candidate MPN; verify 6.3mm body and 2.5mm lead spacing
H1 H2 H3 H4,4,Generic,M3 nylon standoff kit,M3 3.2mm mounting hardware,,Choose length after module and cable clearance measurement
CABLES,1,Generic,2.54mm female-female jumper harness set,Short keyed and labeled harnesses,,Length and connector retention need assembly review
SD1,1,Generic,3.3V microSD card 4-32GB,Offline signed firmware transport,,Untrusted storage; bounded driver and format pending
J1,1,Samtec,TSW-120-07-G-D,DK2 CN1 extension carrier pin header,https://www.samtec.com/products/tsw,Verify mating height and pin numbering before release
J2,1,Samtec,TSW-110-07-G-S,DK2 CN4 digital carrier pin header,https://www.samtec.com/products/tsw,Verify mating height and pin numbering before release
J3,1,Samtec,TSW-108-07-G-S,DK2 CN6 digital carrier pin header,https://www.samtec.com/products/tsw,Verify mating height and pin numbering before release
J4,1,Samtec,TSW-106-07-G-S,DK2 CN7 analog carrier pin header,https://www.samtec.com/products/tsw,Verify mating height and pin numbering before release
J5,1,Samtec,TSW-108-07-G-S,DK2 CN5 power carrier pin header,https://www.samtec.com/products/tsw,Verify mating height and pin numbering before release
J6,1,Samtec,TSW-112-07-G-S,WM8960 digital harness carrier pin header,https://www.samtec.com/products/tsw,Verify mating height and pin numbering before release
J7,1,Samtec,TSW-106-07-G-S,nRF52840 radio harness carrier pin header,https://www.samtec.com/products/tsw,Verify mating height and pin numbering before release
J8,1,Samtec,TSW-107-07-G-S,TROPIC Click harness carrier pin header,https://www.samtec.com/products/tsw,Verify mating height and pin numbering before release
J9,1,Samtec,TSW-104-07-G-S,OPTIGA Trust M harness carrier pin header,https://www.samtec.com/products/tsw,Verify mating height and pin numbering before release
J10,1,Samtec,TSW-106-07-G-S,microSD SPI harness carrier pin header,https://www.samtec.com/products/tsw,Verify mating height and pin numbering before release
J11,1,Samtec,TSW-106-07-G-S,Codec analog harness carrier pin header,https://www.samtec.com/products/tsw,Verify mating height and pin numbering before release
J12,1,Samtec,TSW-104-07-G-S,CTIA headset harness carrier pin header,https://www.samtec.com/products/tsw,Verify mating height and pin numbering before release
J13,1,Samtec,TSW-102-07-G-S,Qi receiver output carrier pin header,https://www.samtec.com/products/tsw,Verify mating height and pin numbering before release
J14,1,Samtec,TSW-104-07-G-S,BQ24074 charger harness carrier pin header,https://www.samtec.com/products/tsw,Verify mating height and pin numbering before release
J15,1,Samtec,TSW-104-07-G-S,5V regulator harness carrier pin header,https://www.samtec.com/products/tsw,Verify mating height and pin numbering before release
J16,1,Samtec,TSW-102-07-G-S,Local update button carrier pin header,https://www.samtec.com/products/tsw,Verify mating height and pin numbering before release
